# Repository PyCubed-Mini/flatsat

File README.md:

# Flatsat
Base circuit board for electrically and mechanically connecting flight hardware. Includes testpoints on all flat flex cable and all camera signals.

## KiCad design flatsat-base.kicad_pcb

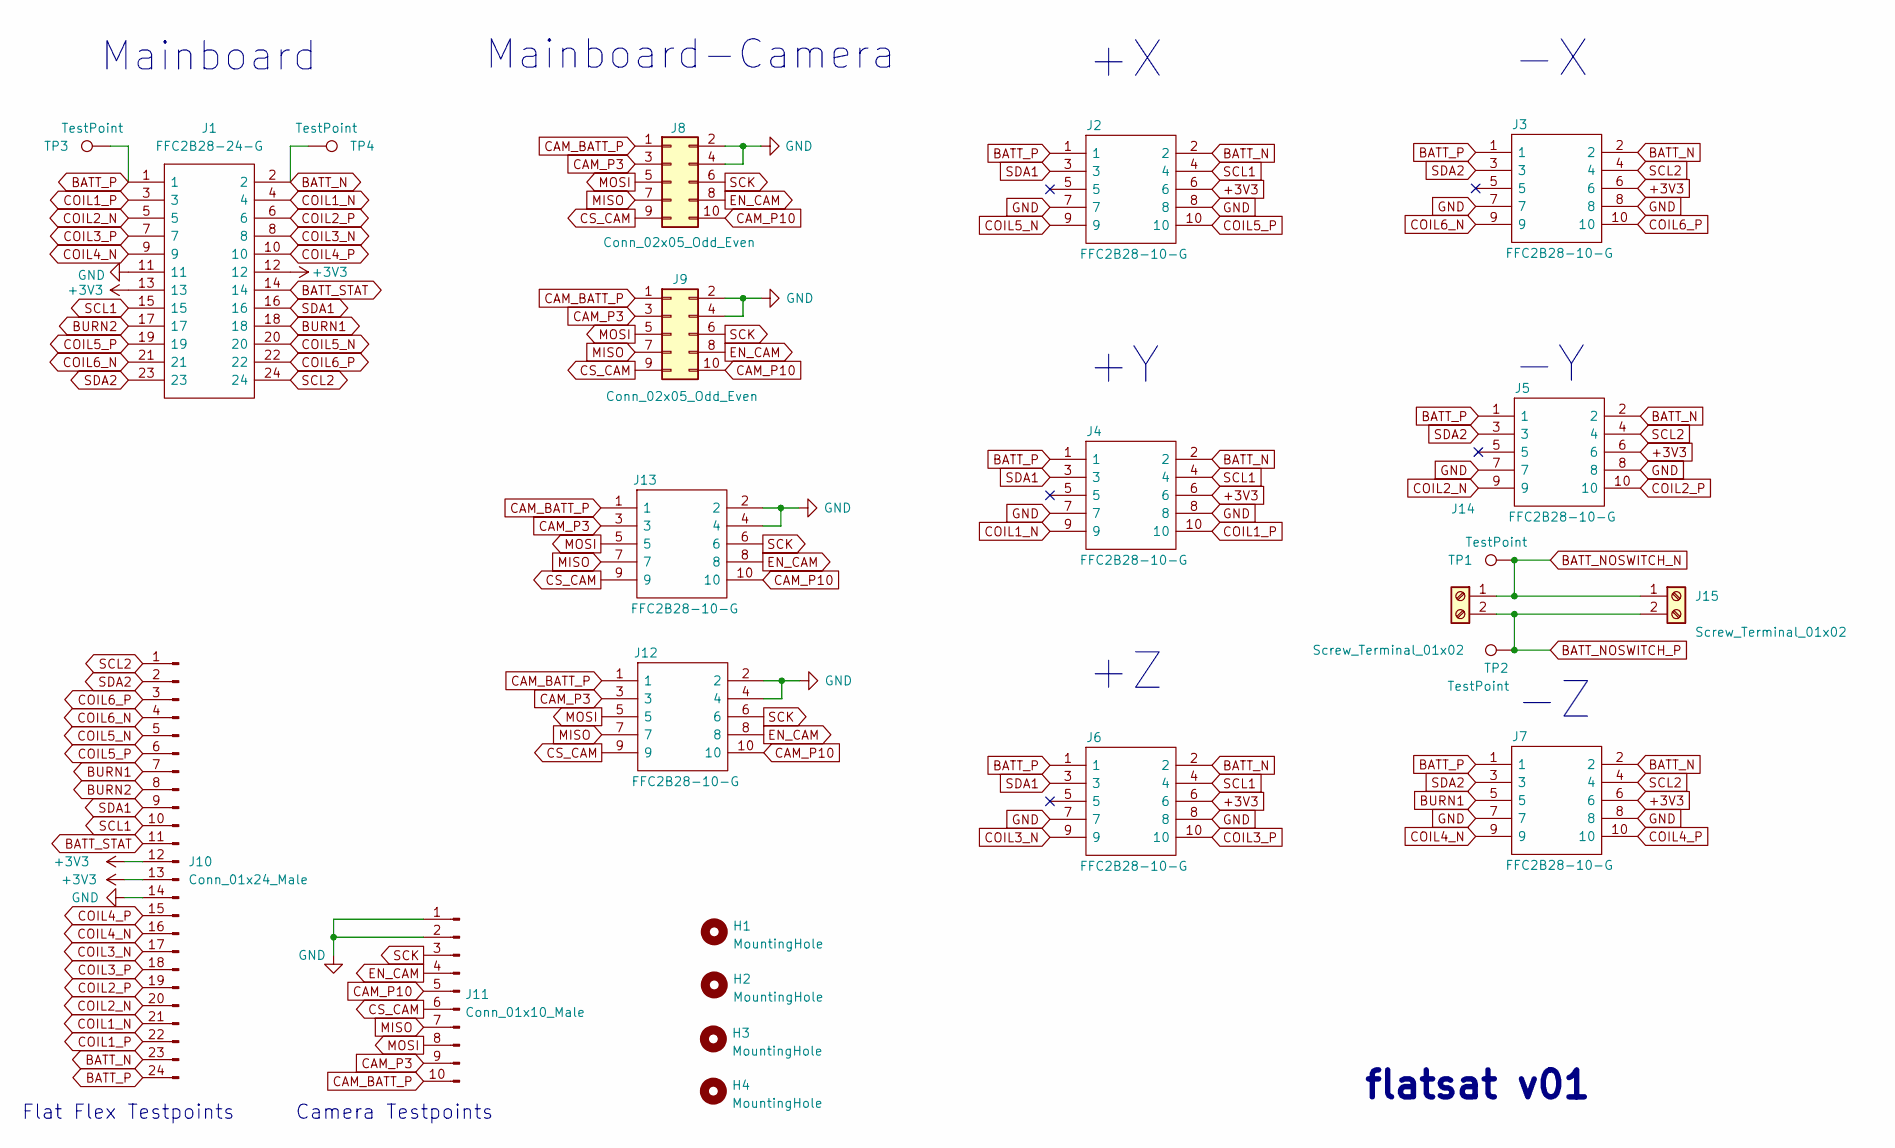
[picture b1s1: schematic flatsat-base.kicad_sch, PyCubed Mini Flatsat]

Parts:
H1, H2, H3, H4: MountingHole; MountingHole_3.2mm_M3_DIN965_Pad
J1: FFC2B28-24-G; GCT_FFC2B28-24-G
J2, J3, J4, J5, J6, J7, J12, J13: FFC2B28-10-G; GCT_FFC2B28-10-G; Manufacturer_Part_Number XF2M-1015-1A; Mouser Part Number 653-XF2M-1015-1A
J8: Conn_02x05_Odd_Even; PinSocket_2x05_P1.27mm_Vertical
J9: Conn_02x05_Odd_Even; PinHeader_2x05_P1.27mm_Vertical
J10: Conn_01x24_Male; PinHeader_1x24_P2.54mm_Vertical
J11: Conn_01x10_Male; PinHeader_1x10_P2.54mm_Vertical
J14, J15: Screw_Terminal_01x02; SCREWTERMINAL-3.5MM-2_LOCK
TP1, TP2, TP3, TP4: TestPoint; TestPoint_Plated_Hole_D5.0mm

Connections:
+3V3: J1.12, J1.13, J2.6, J3.6, J4.6, J5.6, J6.6, J7.6, J10.12, J10.13
BATT_N: J1.2, J2.2, J3.2, J4.2, J5.2, J6.2, J7.2, J10.23, TP4.1
BATT_NOSWITCH_N: J14.1, J15.1, TP1.1
BATT_NOSWITCH_P: J14.2, J15.2, TP2.1
BATT_P: J1.1, J2.1, J3.1, J4.1, J5.1, J6.1, J7.1, J10.24, TP3.1
BATT_STAT: J1.14, J10.11
BURN1: J1.18, J7.5, J10.7
BURN2: J1.17, J10.8
CAM_BATT_P: J8.1, J9.1, J11.10, J12.1, J13.1
CAM_P3: J8.3, J9.3, J11.9, J12.3, J13.3
CAM_P10: J8.10, J9.10, J11.5, J12.10, J13.10
COIL1_N: J1.4, J4.9, J10.21
COIL1_P: J1.3, J4.10, J10.22
COIL2_N: J1.5, J5.9, J10.20
COIL2_P: J1.6, J5.10, J10.19
COIL3_N: J1.8, J6.9, J10.17
COIL3_P: J1.7, J6.10, J10.18
COIL4_N: J1.9, J7.9, J10.16
COIL4_P: J1.10, J7.10, J10.15
COIL5_N: J1.20, J2.9, J10.5
COIL5_P: J1.19, J2.10, J10.6
COIL6_N: J1.21, J3.9, J10.4
COIL6_P: J1.22, J3.10, J10.3
CS_CAM: J8.9, J9.9, J11.6, J12.9, J13.9
EN_CAM: J8.8, J9.8, J11.4, J12.8, J13.8
GND: J1.11, J2.7, J2.8, J3.7, J3.8, J4.7, J4.8, J5.7, J5.8, J6.7, J6.8, J7.7, J7.8, J8.2, J8.4, J9.2, J9.4, J10.14, J11.1, J11.2, J12.2, J12.4, J13.2, J13.4
MISO: J8.7, J9.7, J11.7, J12.7, J13.7
MOSI: J8.5, J9.5, J11.8, J12.5, J13.5
SCK: J8.6, J9.6, J11.3, J12.6, J13.6
SCL1: J1.15, J2.4, J4.4, J6.4, J10.10
SCL2: J1.24, J3.4, J5.4, J7.4, J10.1
SDA1: J1.16, J2.3, J4.3, J6.3, J10.9
SDA2: J1.23, J3.3, J5.3, J7.3, J10.2

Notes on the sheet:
Camera Testpoints
Mainboard
Mainboard-Camera
flatsat v01
Flat Flex Testpoints

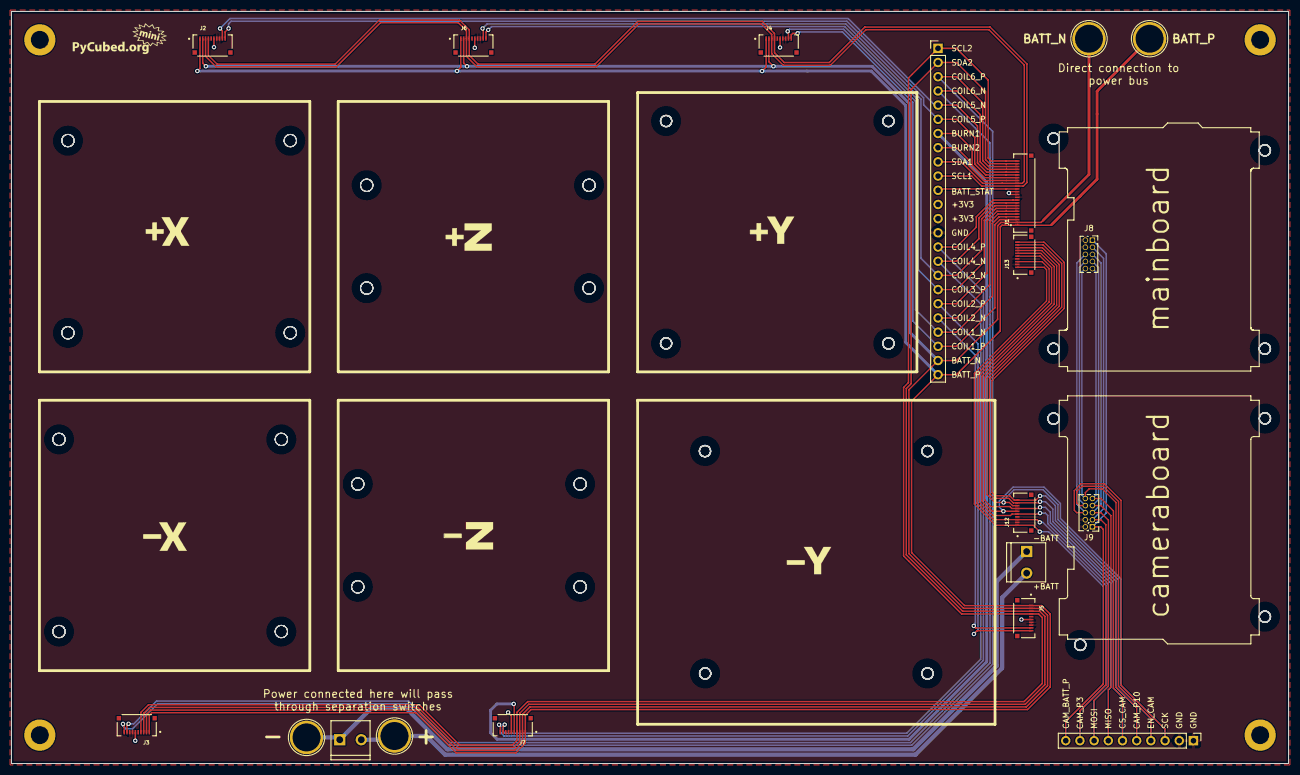
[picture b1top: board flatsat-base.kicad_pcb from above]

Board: 2 copper layers, 228.6 x 134.6 mm, 28 parts (0 on the bottom side), 33 nets.

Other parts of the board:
Ref**: Val**; ypanel
Ref**#2, Ref**#3, Ref**#4: Val**; ypanel
Ref**#5: Val**; pycubed_mini_logo

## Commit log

2022-02-21 flatsat schematic
2022-02-21 ignore auto_saved_files
2022-02-23 svg outlines of all boards
2022-02-23 PCB outline and footprint locations defined, needs routing
2022-02-23 ignore stuff
2022-02-24 Trace widths and other tweaks
2022-02-24 top view 3D render
2022-03-24 Shrank board size a little for cheaper production
2022-03-24 Partially routed
2022-03-25 Finished routing
2022-03-26 Fixed Pinout on mainboard connector, added redundant flat-flex connector
2022-03-28 Added Mounting Holes on main and camera boards
2022-03-29 Fixed some clearance issues, and re-routed Batt_P line
2022-03-29 ignore prl file
2022-04-01 Separated Batt_P and Cam_Batt_P, added FFC connector and realigned
2022-04-01 add battery connector and aligator clip points
2022-04-03 Attachment points for BATT_P/BATT_N and routed
2022-04-07 misc changes
